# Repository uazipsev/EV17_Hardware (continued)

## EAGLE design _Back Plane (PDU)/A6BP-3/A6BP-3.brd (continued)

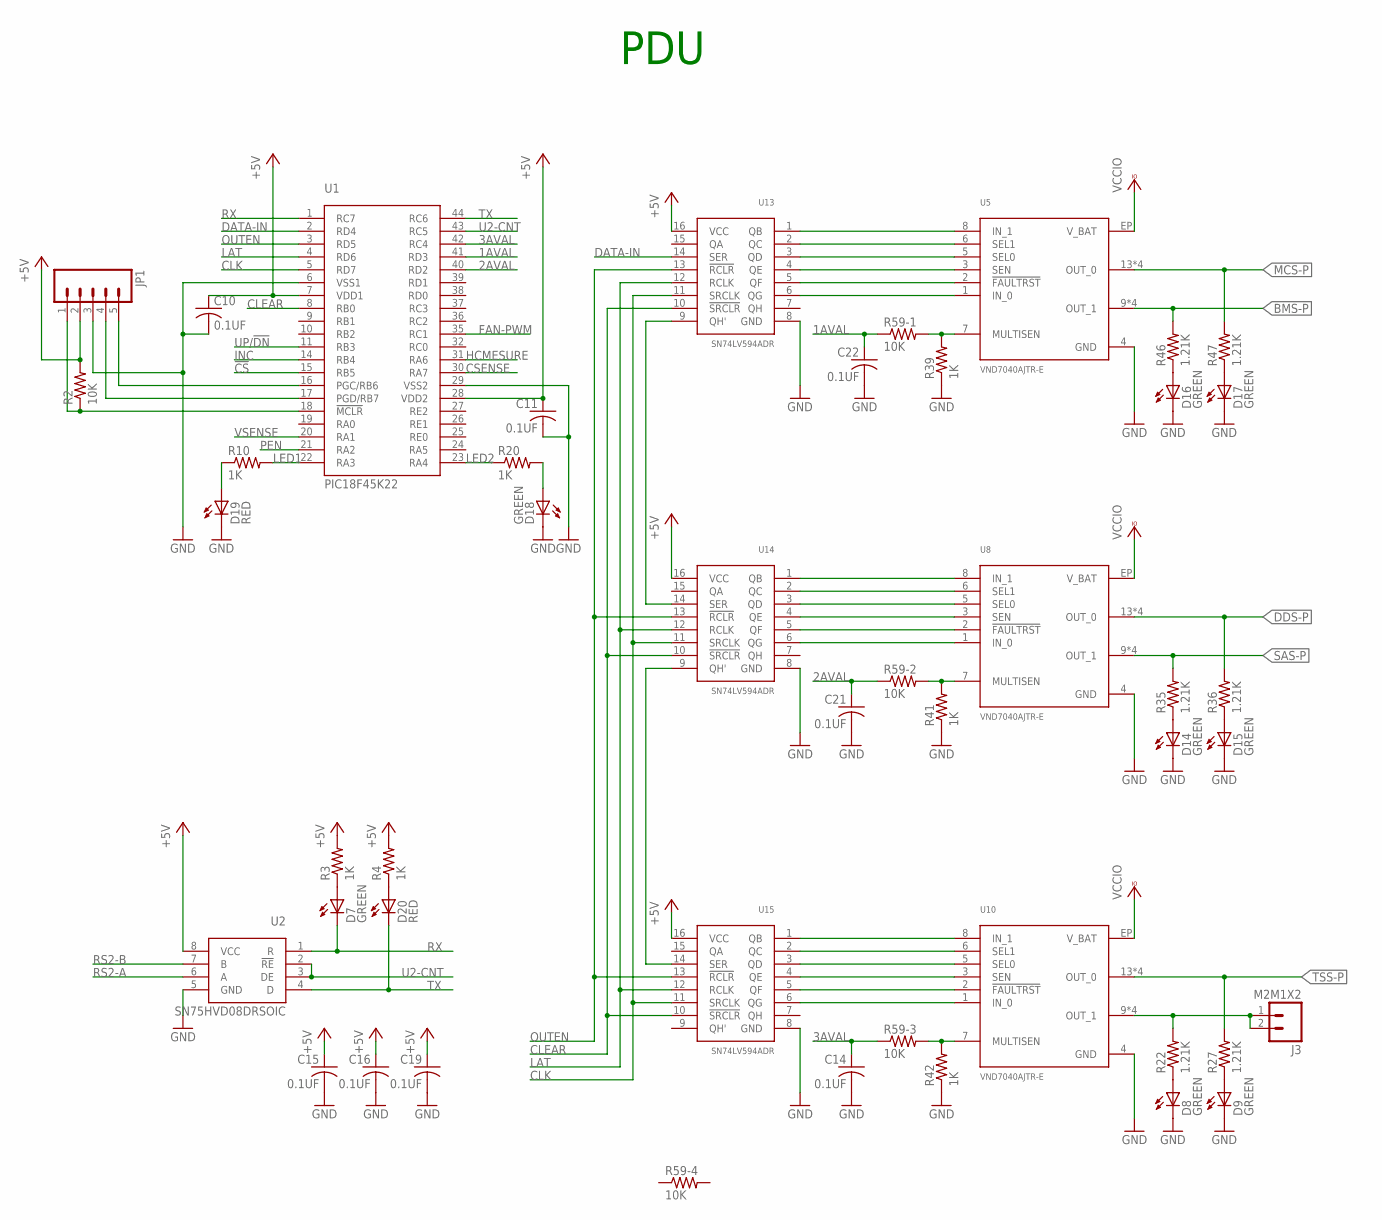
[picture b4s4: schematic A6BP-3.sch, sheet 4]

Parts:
C10, C11, C14, C15, C16, C19, C21, C22: 0.1UF; 0805
D7, D8, D9, D14, D15, D16, D17, D18: GREEN; CHIP_LED0805
D19, D20: RED; CHIP_LED0805
J3: M2M1X2; MOLEX-1X2
JP1: M05LOCK_LONGPADS; 1X05_LOCK_LONGPADS
R2: 10K; 0805
R3, R4, R10, R20, R39, R41, R42: 1K; 0805
R22, R27, R35, R36, R46, R47: 1.21K; 0805
R59: 10K; MNR14
U1: PIC18F45K22; TQFP-44
U2: SN75HVD08DRSOIC; SO-8
U5, U8, U10: VND7040AJTR-E; SSO-16-POWER
U13, U14, U15: SN74LV594ADR; SO-16

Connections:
1AVAL: C22.1 (+), R59.1, U1.41 (RD3)
2AVAL: C21.1 (+), R59.2 (1), U1.40 (RD2)
3AVAL: C14.1 (+), R59.3 (1), U1.42 (RC4)
!CS: U1.15 (RB5); also elsewhere on the board
+5V: C10.1 (+), C11.1 (+), C15.1 (+), C16.1 (+), C19.1 (+), JP1.2, R2.2, R3.2, R4.2, U1.7 (VDD1), U1.28 (VDD2), U2.8 (VCC), U13.16 (VCC), U14.16 (VCC), U15.16 (VCC); also elsewhere on the board
BMS-P: R46.2, U5.9 (OUT_1), U5.10 (OUT_1), U5.11 (OUT_1), U5.12 (OUT_1); also elsewhere on the board
CLEAR: U1.8 (RB0), U13.10 (!SRCLR), U14.10 (!SRCLR), U15.10 (!SRCLR)
CLK: U1.5 (RD7), U13.11 (SRCLK), U14.11 (SRCLK), U15.11 (SRCLK)
CSENSE: U1.30 (RA7); also elsewhere on the board
DATA-IN: U1.2 (RD4), U13.14 (SER)
DDS-P: R36.2, U8.13 (OUT_0), U8.14 (OUT_0), U8.15 (OUT_0), U8.16 (OUT_0); also elsewhere on the board
FAN-PWM: U1.35 (RC1); also elsewhere on the board
GND: C10.2 (-), C11.2 (-), C14.2 (-), C15.2 (-), C16.2 (-), C19.2 (-), C21.2 (-), C22.2 (-), D8.C, D9.C, D14.C, D15.C, D16.C, D17.C, D18.C, D19.C, JP1.3, R39.1, R41.1, R42.1, U1.6 (VSS1), U1.29 (VSS2), U2.5 (GND), U5.4 (GND), U8.4 (GND), U10.4 (GND), U13.8 (GND), U14.8 (GND), U15.8 (GND); also elsewhere on the board
HCMESURE: U1.31 (RA6); also elsewhere on the board
INC: U1.14 (RB4); also elsewhere on the board
LAT: U1.4 (RD6), U13.12 (RCLK), U14.12 (RCLK), U15.12 (RCLK)
LED1: R10.2, U1.22 (RA3)
LED2: R20.1, U1.23 (RA4)
MCS-P: R47.2, U5.13 (OUT_0), U5.14 (OUT_0), U5.15 (OUT_0), U5.16 (OUT_0); also elsewhere on the board
unnamed: U5.8 (IN_1), U13.1 (QB)
unnamed: D19.A, R10.1
unnamed: J3.1, J3.2, R22.2, U10.9 (OUT_1), U10.10 (OUT_1), U10.11 (OUT_1), U10.12 (OUT_1)
unnamed: D7.A, R3.1
unnamed: D20.A, R4.1
unnamed: D8.A, R22.1
unnamed: D9.A, R27.1
unnamed: R42.2, R59.6 (2), U10.7 (MULTISEN)
unnamed: U5.6 (SEL1), U13.2 (QC)
unnamed: U5.5 (SEL0), U13.3 (QD)
unnamed: U5.3 (SEN), U13.4 (QE)
unnamed: JP1.4, U1.17 (PGD/RB7)
unnamed: JP1.5, U1.16 (PGC/RB6)
unnamed: U5.2 (!FAULTRST), U13.5 (QF)
unnamed: JP1.1, R2.1, U1.18 (!MCLR)
unnamed: D18.A, R20.2
unnamed: U13.9 (QH'), U14.14 (SER)
unnamed: U5.1 (IN_0), U13.6 (QG)
unnamed: U8.8 (IN_1), U14.1 (QB)
unnamed: U8.6 (SEL1), U14.2 (QC)
unnamed: U8.5 (SEL0), U14.3 (QD)
unnamed: D14.A, R35.1
unnamed: D15.A, R36.1
unnamed: R39.2, R59.8 (2), U5.7 (MULTISEN)
unnamed: U8.3 (SEN), U14.4 (QE)
unnamed: U8.2 (!FAULTRST), U14.5 (QF)
unnamed: U8.1 (IN_0), U14.6 (QG)
unnamed: U10.8 (IN_1), U15.1 (QB)
unnamed: U10.6 (SEL1), U15.2 (QC)
unnamed: U10.5 (SEL0), U15.3 (QD)
unnamed: U10.3 (SEN), U15.4 (QE)
unnamed: U10.2 (!FAULTRST), U15.5 (QF)
unnamed: U10.1 (IN_0), U15.6 (QG)
unnamed: D16.A, R46.1
unnamed: U14.9 (QH'), U15.14 (SER)
unnamed: D17.A, R47.1
unnamed: R41.2, R59.7 (2), U8.7 (MULTISEN)
OUTEN: U1.3 (RD5), U13.13 (!RCLR), U14.13 (!RCLR), U15.13 (!RCLR)
PEN: U1.21 (RA2)
RS2-A: U2.6 (A); also elsewhere on the board
RS2-B: U2.7 (B); also elsewhere on the board
RX: D7.C, U1.1 (RC7), U2.1 (R)
SAS-P: R35.2, U8.9 (OUT_1), U8.10 (OUT_1), U8.11 (OUT_1), U8.12 (OUT_1); also elsewhere on the board
TSS-P: R27.2, U10.13 (OUT_0), U10.14 (OUT_0), U10.15 (OUT_0), U10.16 (OUT_0); also elsewhere on the board
TX: D20.C, U1.44 (RC6), U2.4 (D)
U2-CNT: U1.43 (RC5), U2.2 (!RE), U2.3 (DE)
UP/!DN: U1.11 (RB3); also elsewhere on the board
VCCIO: U5.EP (V_BAT), U8.EP (V_BAT), U10.EP (V_BAT); also elsewhere on the board
VSENSE: U1.20 (RA1); also elsewhere on the board

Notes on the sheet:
PDU

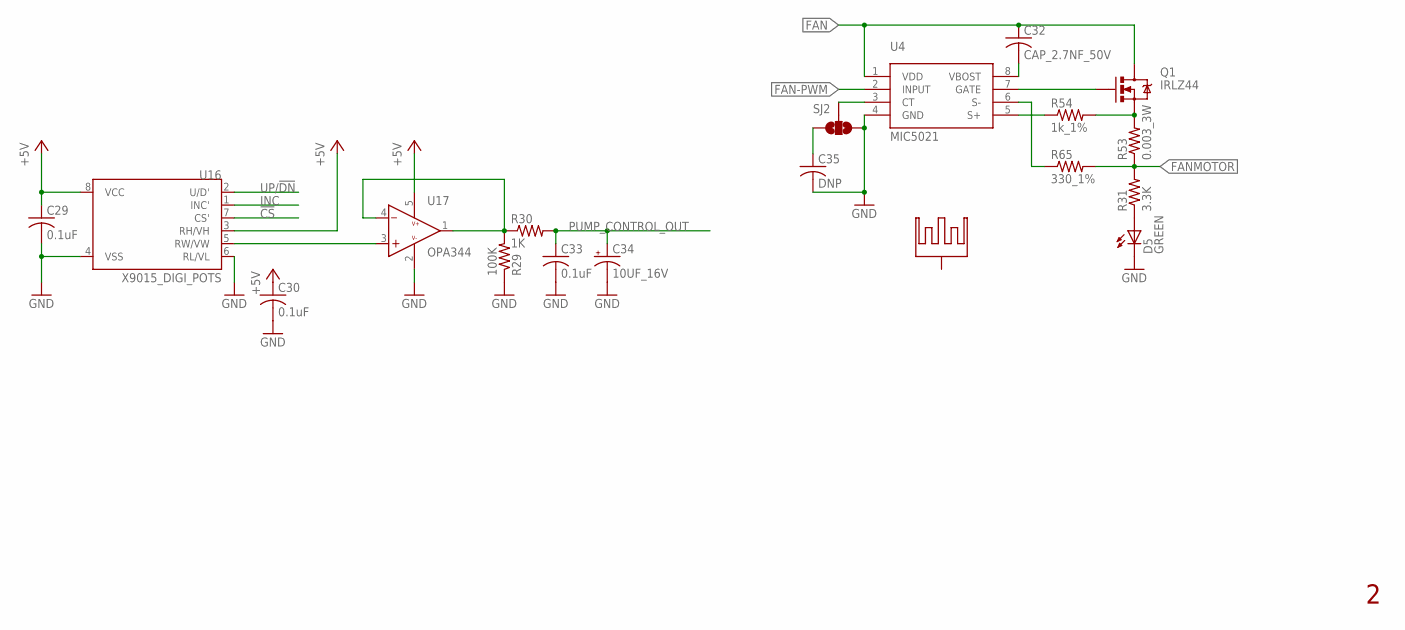
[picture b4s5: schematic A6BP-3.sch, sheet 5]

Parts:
C29, C30, C33: 0.1uF; 0805
C32: CAP_2.7NF_50V; 0805
C34: 10UF_16V; EIA3216-16V
C35: DNP; 0805
D5: GREEN; CHIP_LED0805
HS1: HEATSINK; 581002B02500G
Q1: IRLZ44; TO-220
R29: 100K; 0805
R30: 1K; 0805
R31: 3.3K; 0805
R53: 0.003_3W; 2512
R54: 1k_1%; 0805
R65: 330_1%; 0805
SJ2: JUMPER-PAD-3-NOFULL_BOX_SILK; PAD-JUMPER-3-NO_YES_SILK_FULL_BOX
U4: MIC5021; SO-8
U16: X9015_DIGI_POTS; SO08; PARTNO X9313WSZT1
U17: OPA344; SOT23-5

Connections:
!CS: U16.7 (CS'); also elsewhere on the board
+5V: C29.1 (+), C30.1 (+), U16.3 (RH/VH), U16.8 (VCC), U17.5 (V+); also elsewhere on the board
FAN: C32.1 (+), Q1.2 (D), U4.1 (VDD); also elsewhere on the board
FAN-PWM: U4.2 (INPUT); also elsewhere on the board
FANMOTOR: R31.2, R53.1, R65.2; also elsewhere on the board
GND: C29.2 (-), C30.2 (-), C33.2 (-), C34.C (-), C35.2 (-), D5.C, R29.1, SJ2.1, U4.4 (GND), U16.4 (VSS), U16.6 (RL/VL), U17.2 (V-); also elsewhere on the board
INC: U16.1 (INC'); also elsewhere on the board
unnamed: U16.5 (RW/VW), U17.3 (+)
unnamed: Q1.1 (G), U4.7 (GATE)
unnamed: D5.A, R31.1
unnamed: SJ2.2, U4.3 (CT)
unnamed: Q1.3 (S), R53.2, R54.2
unnamed: R54.1, U4.5 (S+)
unnamed: R65.1, U4.6 (S-)
unnamed: C32.2 (-), U4.8 (VBOST)
unnamed: C35.1 (+), SJ2.3
PUMP_CONTROL_OUT: C33.1 (+), C34.A (+), R30.2; also elsewhere on the board
PUMP_OUTPUT_CONTROL: R29.2, R30.1, U17.1 (O), U17.4 (-)
UP/!DN: U16.2 (U/D'); also elsewhere on the board

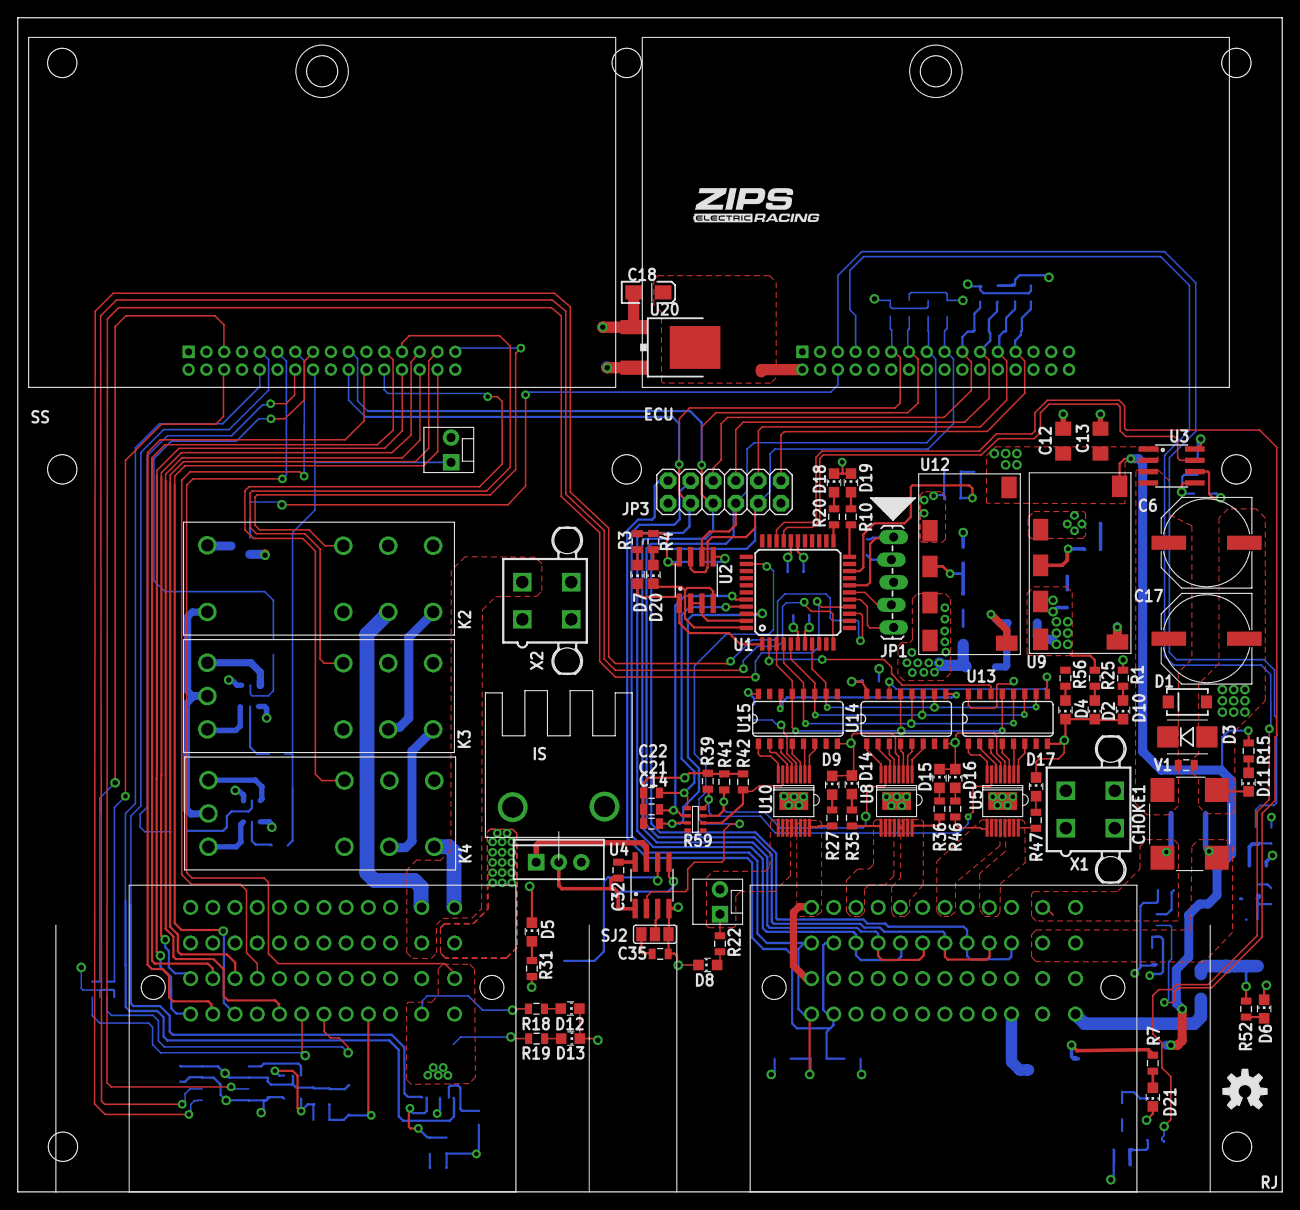
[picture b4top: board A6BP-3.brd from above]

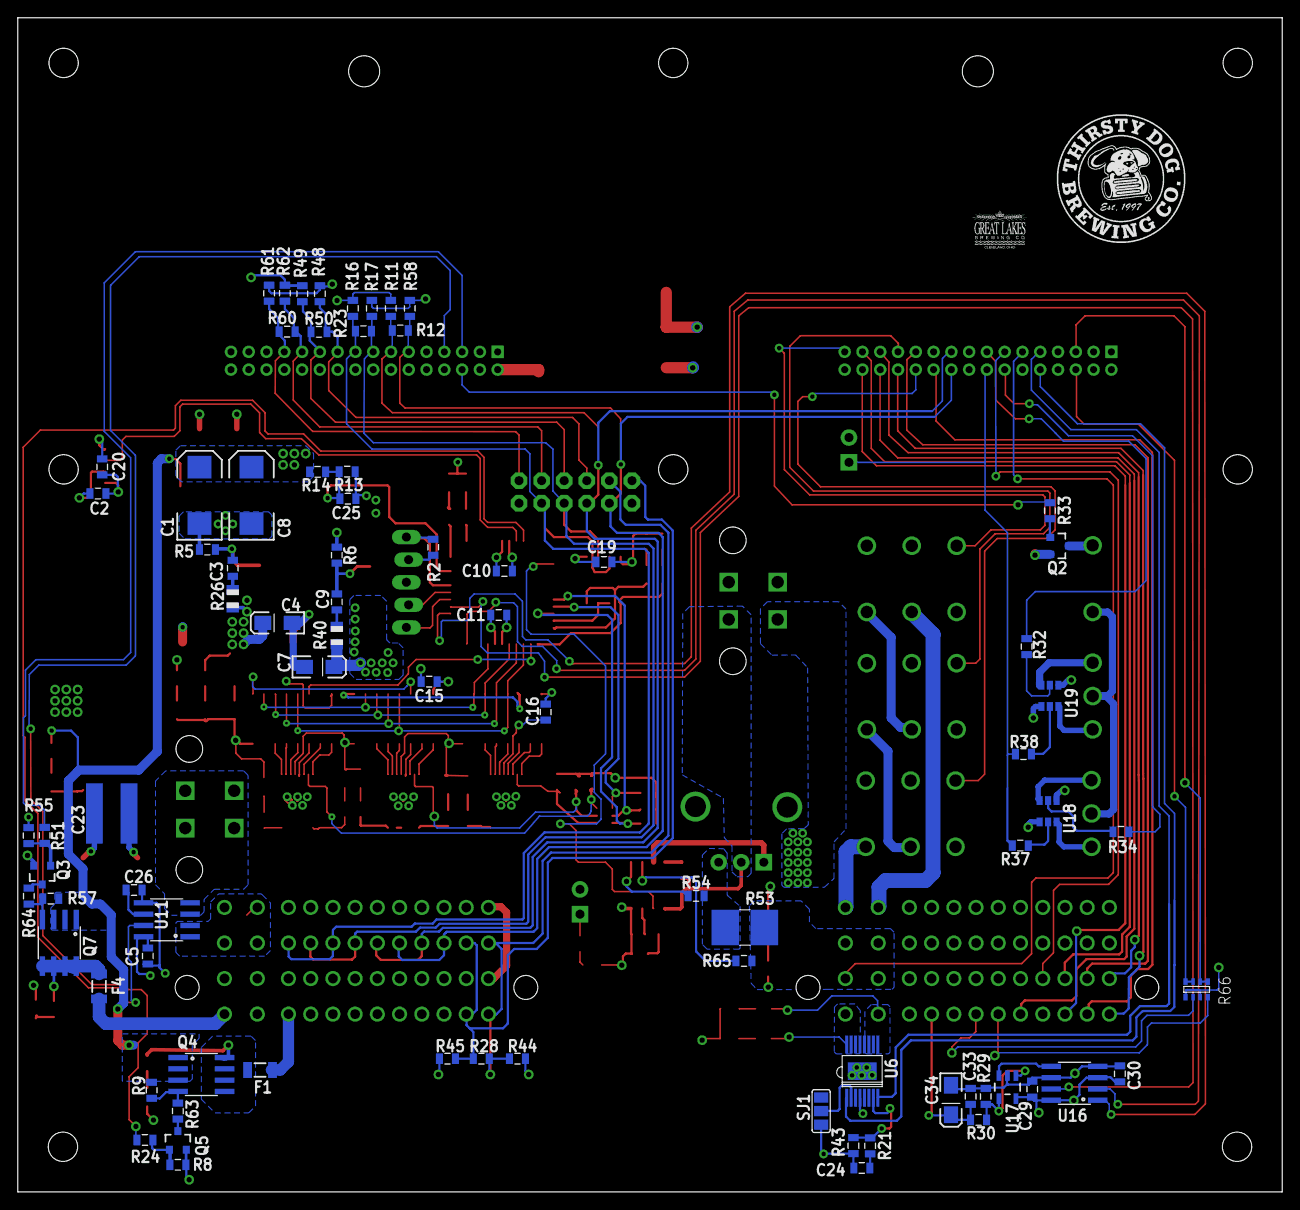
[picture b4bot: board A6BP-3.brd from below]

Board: 4 copper layers, 142.2 x 132.1 mm, 178 parts (81 on the bottom side), 163 nets.

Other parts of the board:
STANDOFF1, STANDOFF4: STAND-OFF
U$1: TD-M
U$2: GL-S
U$3: 2016-LOGO-L
U$4: 2016-2-LOGO-L

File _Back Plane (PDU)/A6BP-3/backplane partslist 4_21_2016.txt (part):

Partlist

Exported from A6BP-3.sch at 4/21/2016 3:48:01 PM

EAGLE Version 7.2.0 Copyright (c) 1988-2014 CadSoft

Assembly variant: 

Part     Value           Device                       Package                           Library               Sheet

C1       10UF            CAP-POL_10UF_60V             EIA7343                           FSAE Electric         1
C2       0.1UF           CAP_0.1UF_50V_0805           0805                              FSAE Electric         1
C3       DNP             CAP0805                      0805                              SparkFun-Capacitors   1
C4       10UF            CAP-POL_10UF_16V             EIA3216-16V                       FSAE Electric         1
C5       0.1UF           CAP_0.1UF_50V_0805           0805                              FSAE Electric         1
C6       100UF_50V       CAP-POL_100UF_50V_SMD        PANASONIC-G                       FSAE Electric         1
C7       10UF            CAP-POL_10UF_16V             EIA3216-16V                       FSAE Electric         1
C8       10UF            CAP-POL_10UF_60V             EIA7343                           FSAE Electric         1
C9       DNP             CAP0805                      0805                              SparkFun-Capacitors   1
C10      0.1UF           CAP_0.1UF_50V_0805           0805                              FSAE Electric         4
C11      0.1UF           CAP_0.1UF_50V_0805           0805                              FSAE Electric         4
C12      1UF             CAP_1UF_50V                  1206@1                            FSAE Electric         1
C13      1UF             CAP_1UF_50V                  1206@1                            FSAE Electric         1
C14      0.1UF           CAP_0.1UF_50V_0805           0805                              FSAE Electric         4
C15      0.1UF           CAP_0.1UF_50V_0805           0805                              FSAE Electric         4
C16      0.1UF           CAP_0.1UF_50V_0805           0805                              FSAE Electric         4
C17      100UF_50V       CAP-POL_100UF_50V_SMD        PANASONIC-G                       FSAE Electric         1
C18      10UF            CAP-POL_10UF_16V             EIA3216-16V                       FSAE Electric         1
C19      0.1UF           CAP_0.1UF_50V_0805           0805                              FSAE Electric         4
C20      0.1UF           CAP_0.1UF_50V_0805           0805                              FSAE Electric         1
C21      0.1UF           CAP_0.1UF_50V_0805           0805                              FSAE Electric         4
C22      0.1UF           CAP_0.1UF_50V_0805           0805                              FSAE Electric         4
C23      1000PF          CAP_1000PF_2KV               C1825                             FSAE Electric         1
C24      0.1UF           CAP_0.1UF_50V_0805           0805                              FSAE Electric         3
C25      1UF             CAP_1UF_50V_0805             0805                              FSAE Electric         1
C26      0.1UF           CAP_0.1UF_50V_0805           0805                              FSAE Electric         1
C29      0.1uF           CAP_0.1UF_50V_0805           0805                              FSAE Electric         5
C30      0.1uF           CAP_0.1UF_50V_0805           0805                              FSAE Electric         5
C32      CAP_2.7NF_50V   CAP_2.7NF_50V                0805                              FSAE Electric         5
C33      0.1uF           CAP_0.1UF_50V_0805           0805                              FSAE Electric         5
C34      10UF_16V        CAP-POL_10UF_16V             EIA3216-16V                       FSAE Electric         5
C35      DNP             CAP_2.7NF_50V                0805                              FSAE Electric         5
CHOKE1   744272471       744272471                    744272471                         FSAE Electric         1
D1       33.3V           TVS_33.3V                    SMA                               FSAE Electric         1
D2       GREEN           LED_GREEN                    CHIP_LED0805                      FSAE Electric         1
D3       33V             DIODE-ZENER_33V              SMB                               FSAE Electric         1
D4       GREEN           LED_GREEN                    CHIP_LED0805                      FSAE Electric         1
D5       GREEN           LED_GREEN                    CHIP_LED0805                      FSAE Electric         5
D6       GREEN           LED_GREEN                    CHIP_LED0805                      FSAE Electric         2
D7       GREEN           LED_GREEN                    CHIP_LED0805                      FSAE Electric         4
D8       GREEN           LED_GREEN                    CHIP_LED0805                      FSAE Electric         4
D9       GREEN           LED_GREEN                    CHIP_LED0805                      FSAE Electric         4
D10      GREEN           LED_GREEN                    CHIP_LED0805                      FSAE Electric         1
D11      GREEN           LED_GREEN                    CHIP_LED0805                      FSAE Electric         1
D12      GREEN           LED_GREEN                    CHIP_LED0805                      FSAE Electric         3
D13      GREEN           LED_GREEN                    CHIP_LED0805                      FSAE Electric         3
D14      GREEN           LED_GREEN                    CHIP_LED0805                      FSAE Electric         4
D15      GREEN           LED_GREEN                    CHIP_LED0805                      FSAE Electric         4
D16      GREEN           LED_GREEN                    CHIP_LED0805                      FSAE Electric         4
D17      GREEN           LED_GREEN                    CHIP_LED0805                      FSAE Electric         4
D18      GREEN           LED_GREEN                    CHIP_LED0805                      FSAE Electric         4
D19      RED             LED_RED                      CHIP_LED0805                      FSAE Electric         4
D20      RED             LED_RED                      CHIP_LED0805                      FSAE Electric         4
D21      GREEN           LED_GREEN                    CHIP_LED0805                      FSAE Electric         2
ECU      CARD-2016RECP   CARD-2016RECP                CARD-2016-RCP                     FSAE Electric         2
F1       PTCSMD          PTCSMD                       PTC-1206                          SparkFun-PowerIC      2
F4       PTCSMD          PTCSMD                       PTC-1206                          SparkFun-PowerIC      2
HS1      HEATSINK        HEATSINK                     581002B02500G                     FSAE Electric         5
J1       36638           36638                        36638                             FSAE Eletric          2
J2       36638           36638                        36638                             FSAE Eletric          2
J3       M2M1X2          M2M1X2                       MOLEX-1X2                         FSAE Electric         4
J4       M2M1X2          M2M1X2                       MOLEX-1X2                         FSAE Electric         3
JP1                      M05LOCK_LONGPADS             1X05_LOCK_LONGPADS                SparkFun-Connectors   4
JP3      2X6 FEMALE      M06X2PTH_FEMALE              2X6                               SparkFun-Connectors   2
K2       RTE44024F       RTE44024F                    RTE44024F                         FSAE Electric         3
K3       RT424F24        RT424F24                     RT424F24                          FSAE Electric         3
K4       RT424F24        RT424F24                     RT424F24                          FSAE Electric         3
Q1       IRLZ44          MOS-N_IRLZ44                 TO-220                            FSAE Electric         5
Q2       NUD3160LT1G     NUD3160LT1G                  SOT23                             FSAE Electric         3
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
